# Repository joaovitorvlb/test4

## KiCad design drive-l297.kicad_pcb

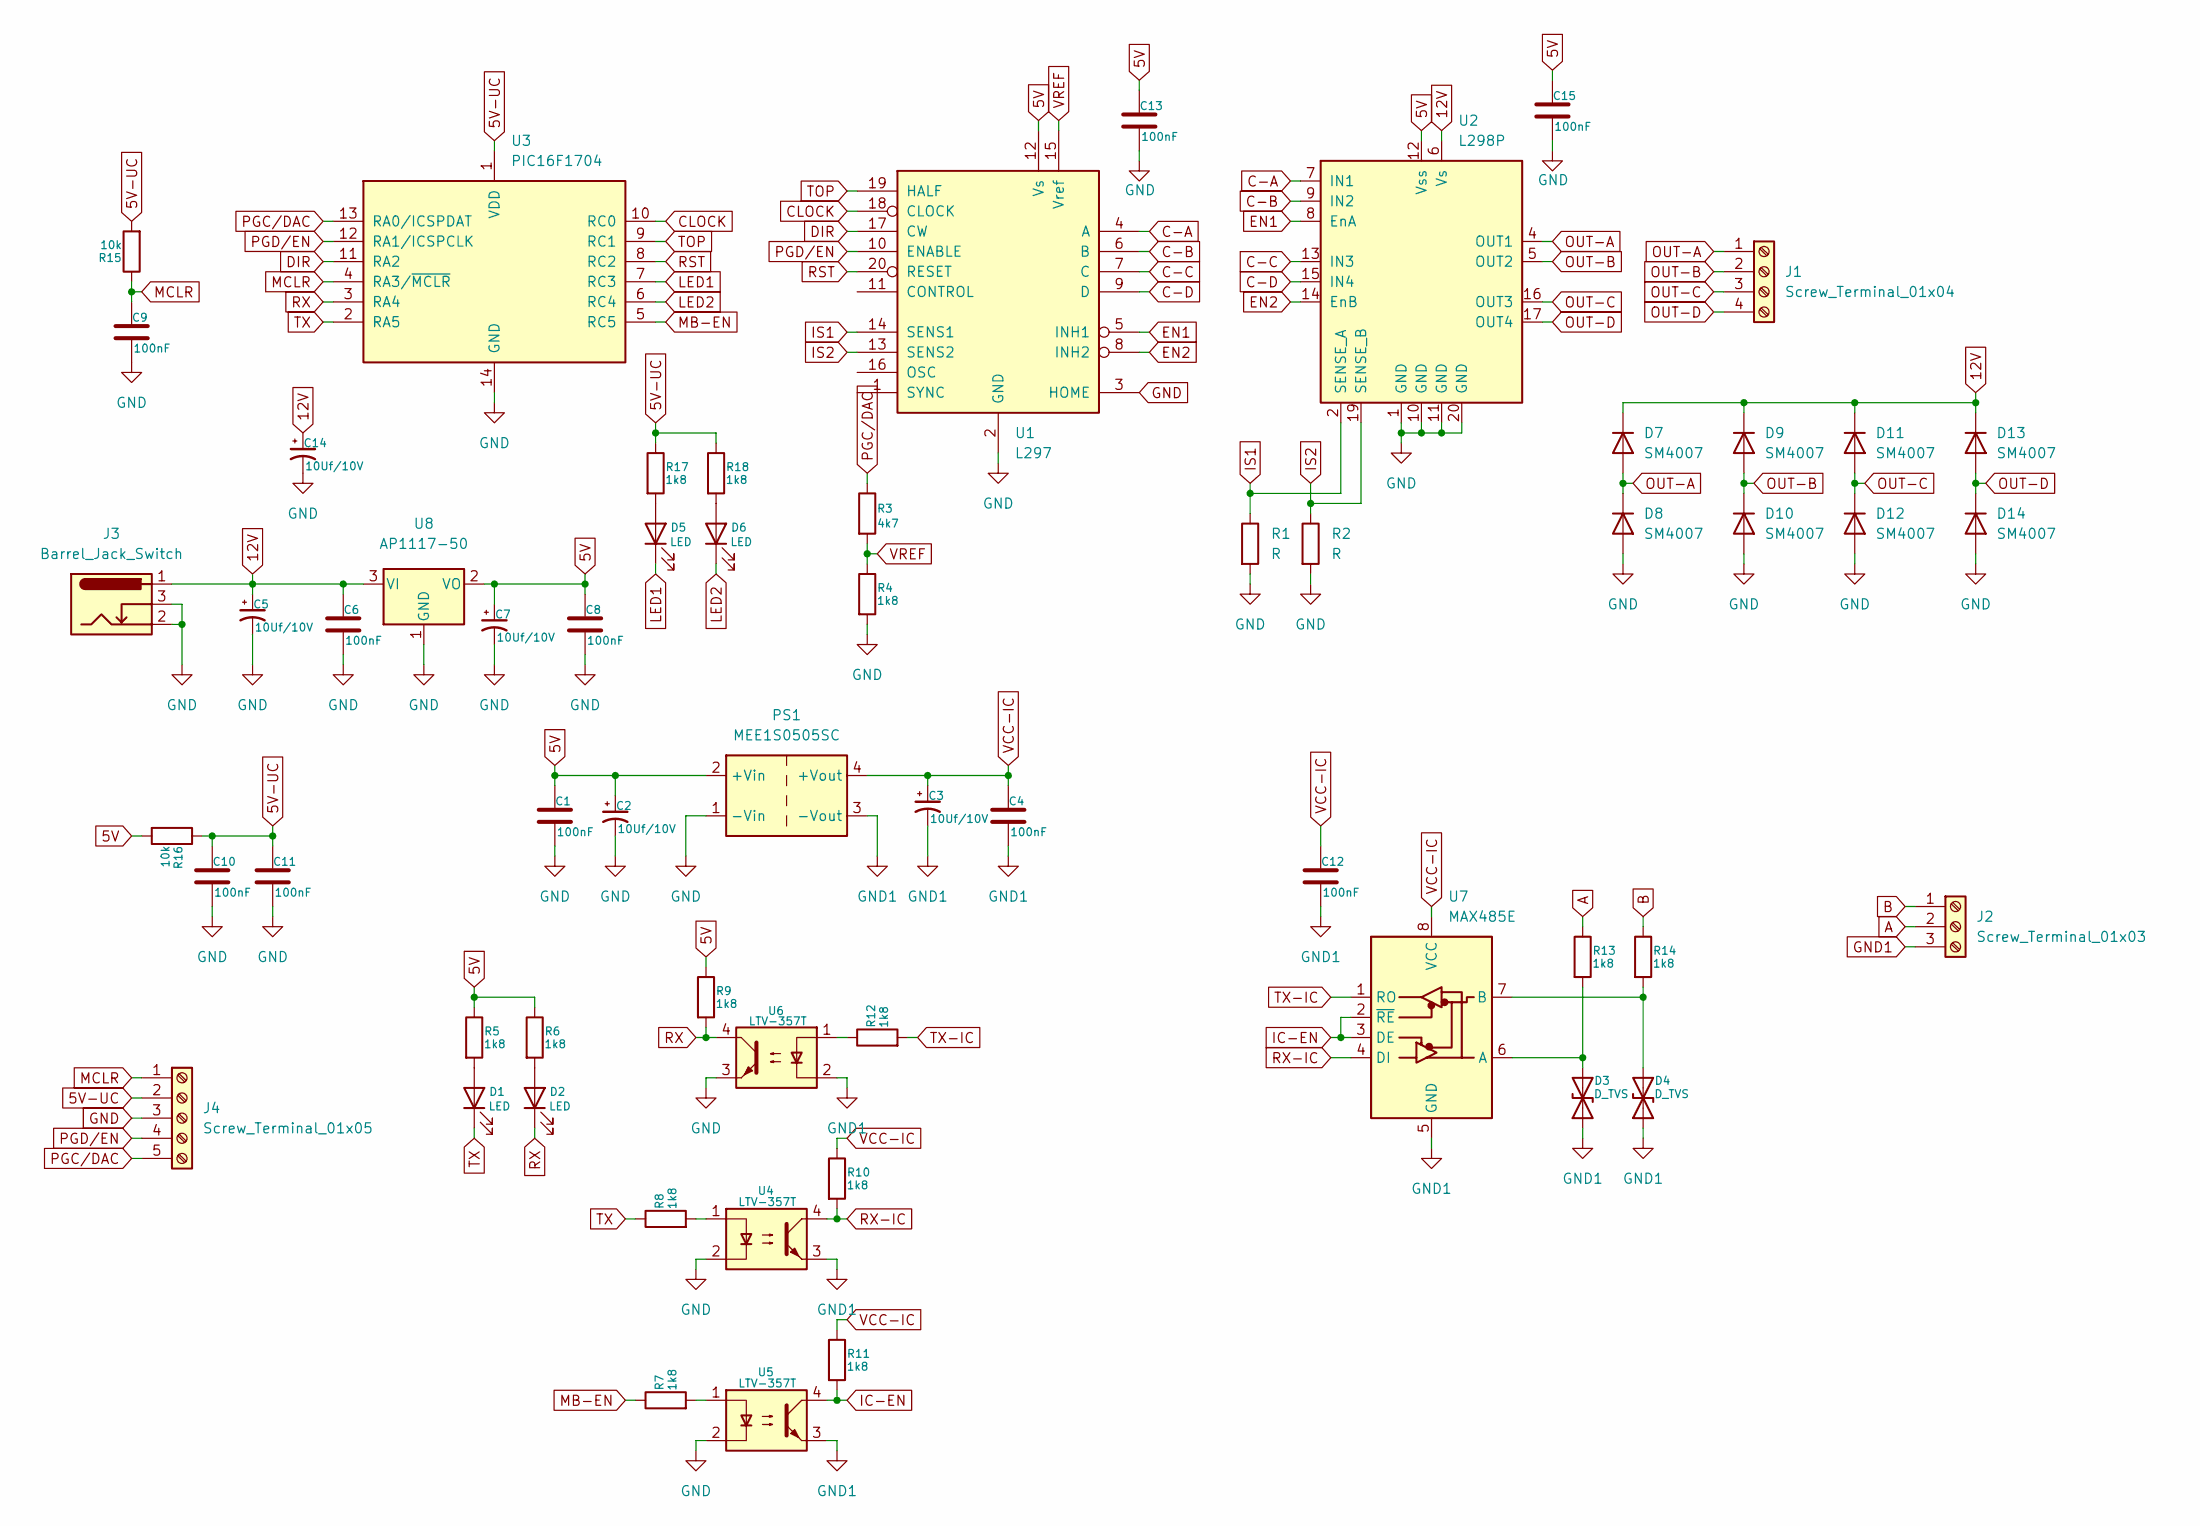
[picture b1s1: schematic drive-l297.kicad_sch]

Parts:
C1, C4, C6, C8, C9, C10, C11, C12, C13, C15: 100nF; C_0805_2012Metric
C2, C3: 10Uf/10V; CP_Elec_4x5.8
C5: 10Uf/10V; CP_Elec_6.3x3
C7: 10Uf/10V; CP_Elec_5x4.4
C14: 10Uf/10V; CP_Elec_10x14.3
D1, D2, D5, D6: LED; LED_0805_2012Metric
D3, D4: D_TVS; D_SOD-128
D7, D8, D9, D10, D11, D12, D13, D14: SM4007; D_MELF
J1: Screw_Terminal_01x04; PinHeader_1x04_P2.54mm_Vertical
J2: Screw_Terminal_01x03; PhoenixContact_MSTBVA_2,5_3-G-5,08_1x03_P5.08mm_Vertical
J3: Barrel_Jack_Switch; BarrelJack_GCT_DCJ200-10-A_Horizontal
J4: Screw_Terminal_01x05; PinHeader_1x05_P2.54mm_Vertical
PS1: MEE1S0505SC; Converter_DCDC_Murata_MEE1SxxxxSC_THT
R1, R2: R; R_2512_6332Metric
R3: 4k7; R_0805_2012Metric
R4, R5, R6, R7, R8, R9, R10, R11, R12, R13, R14, R17, R18: 1k8; R_0805_2012Metric
R15: 10k; R_0805_2012Metric
R16: 10k; R_1206_3216Metric
U1: L297; HSOP-20-1EP_11.0x15.9mm_P1.27mm_SlugUp
U2: L298P; HSOP-20-1EP_11.0x15.9mm_P1.27mm_SlugDown_ThermalVias
U3: PIC16F1704; SO-14_3.9x8.65mm_P1.27mm
U4, U5, U6: LTV-357T; SO-4_4.4x3.6mm_P2.54mm
U7: MAX485E; PowerIntegrations_SO-8
U8: AP1117-50; SOT-223-3_TabPin2

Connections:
5V: C1.1, C2.1, C7.1, C8.1, C13.1, C15.1, PS1.2 (+Vin), R5.1, R6.1, R9.1, R16.2, U1.12 (Vs), U2.12 (Vss), U8.2 (VO)
5V-UC: C10.1, C11.1, J4.2, R15.2, R16.1, R17.1, R18.1, U3.1 (VDD)
12V: C5.1, C6.1, C14.1, D7.1 (K), D9.1 (K), D11.1 (K), D13.1 (K), J3.1, U2.6 (Vs), U8.3 (VI)
A: J2.2, R13.1
B: J2.1, R14.1
C-A: U1.4 (A), U2.7 (IN1)
C-B: U1.6 (B), U2.9 (IN2)
C-C: U1.7 (C), U2.13 (IN3)
C-D: U1.9 (D), U2.15 (IN4)
CLOCK: U1.18 (CLOCK), U3.10 (RC0)
DIR: U1.17 (CW), U3.11 (RA2)
EN1: U1.5 (INH1), U2.8 (EnA)
EN2: U1.8 (INH2), U2.14 (EnB)
GND: C1.2, C2.2, C5.2, C6.2, C7.2, C8.2, C9.2, C10.2, C11.2, C13.2, C14.2, C15.2, D8.2 (A), D10.2 (A), D12.2 (A), D14.2 (A), J3.2, J3.3, J4.3, PS1.1 (-Vin), R1.2, R2.2, R4.2, U1.2 (GND), U1.3 (HOME), U2.1 (GND), U2.10 (GND), U2.11 (GND), U2.20 (GND), U3.14 (GND), U4.2, U5.2, U6.3, U8.1 (GND)
GND1: C3.2, C4.2, C12.2, D3.1 (A1), D4.1 (A1), J2.3, PS1.3 (-Vout), U4.3, U5.3, U6.2, U7.5 (GND)
IC-EN: R11.2, U5.4, U7.2 (~RE), U7.3 (DE)
IS1: R1.1, U1.14 (SENS1), U2.2 (SENSE_A)
IS2: R2.1, U1.13 (SENS2), U2.19 (SENSE_B)
LED1: D5.1 (K), U3.7 (RC3)
LED2: D6.1 (K), U3.6 (RC4)
MB-EN: R7.1, U3.5 (RC5)
MCLR: C9.1, J4.1, R15.1, U3.4 (RA3/~MCLR)
unnamed: D1.2 (A), R5.2
unnamed: D2.2 (A), R6.2
unnamed: D3.2 (A2), R13.2, U7.6 (A)
unnamed: D4.2 (A2), R14.2, U7.7 (B)
unnamed: D5.2 (A), R17.2
unnamed: D6.2 (A), R18.2
unnamed: R7.2, U5.1
unnamed: R8.2, U4.1
unnamed: R12.1, U6.1
OUT-A: D7.2 (A), D8.1 (K), J1.1, U2.4 (OUT1)
OUT-B: D9.2 (A), D10.1 (K), J1.2, U2.5 (OUT2)
OUT-C: D11.2 (A), D12.1 (K), J1.3, U2.16 (OUT3)
OUT-D: D13.2 (A), D14.1 (K), J1.4, U2.17 (OUT4)
PGC/DAC: J4.5, R3.1, U3.13 (RA0/ICSPDAT)
PGD/EN: J4.4, U1.10 (ENABLE), U3.12 (RA1/ICSPCLK)
RST: U1.20 (RESET), U3.8 (RC2)
RX: D2.1 (K), R9.2, U3.3 (RA4), U6.4
RX-IC: R10.2, U4.4, U7.4 (DI)
TOP: U1.19 (HALF), U3.9 (RC1)
TX: D1.1 (K), R8.1, U3.2 (RA5)
TX-IC: R12.2, U7.1 (RO)
VCC-IC: C3.1, C4.1, C12.1, PS1.4 (+Vout), R10.1, R11.1, U7.8 (VCC)
VREF: R3.2, R4.1, U1.15 (Vref)

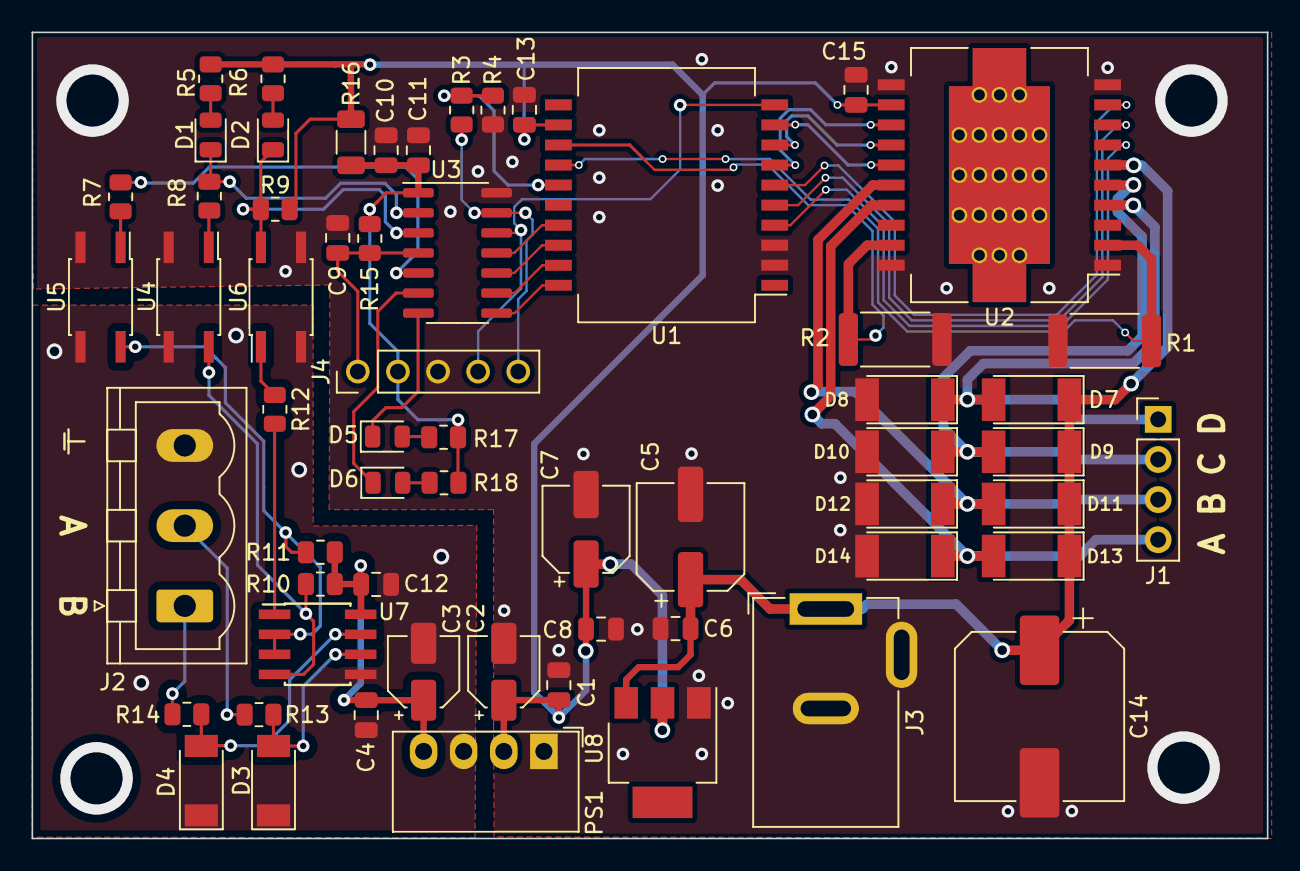
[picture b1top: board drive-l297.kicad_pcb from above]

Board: 2 copper layers, 78.2 x 51.1 mm, 60 parts (0 on the bottom side), 45 nets.

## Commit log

2023-06-23 Adicionando conteúdo da pasta ao repositório
